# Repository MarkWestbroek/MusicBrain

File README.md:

# MusicBrain

An open platform for playable instruments, recallable patches and musical
control. Build and play modular patches in your browser, run shared DSP on a
Teensy, and connect supported external hardware through MIDI, CV, gates and
relay switching.

MusicBrain started as a way to give analog rigs memory. It now also includes
digital synthesizers, samplers and effects. External audio paths can remain
analog; internal DSP and USB audio are digital. Recall of external equipment
depends on which parameters and connections its hardware can actually control.

**[Open the editor](https://editor.musicbrain.nl/)** ([in English](https://editor.musicbrain.nl/?lang=en)) ·
[Website](https://musicbrain.nl/) ·
[Firmware downloads](https://github.com/MarkWestbroek/MusicBrain/releases) ·
[Development log](doc/RELEASE-LOG.md)

## Start here

| I want to... | Start with |
|---|---|
| Hear and edit a patch without hardware | [Try it in the browser](#try-it-in-the-browser) |
| Play patches on a Teensy | [Use a Teensy](#use-a-teensy) |
| Build or extend the hardware | [Build hardware](#build-hardware) |
| Explore instruments and workflows | [Feature guide](#feature-guide) |
| Work on the code | [Develop locally](#develop-locally) |
| Understand the direction | [Where it is going](#where-it-is-going) |

## Current status

**Development snapshot: 9 October 2026.** This is an active development
project, not just scaffolding and not a finished hardware product family.
The firmware source identifies itself as **0.5.99**. The deployed editor,
downloadable firmware and published hardware releases can lag behind source;
check the release notes and the version reported by a connected device.

| Product | Name used in this repository/editor | Current scope |
|---|---|---|
| **Cortex** | Modular MB / MMB / modular-brain | Working rack editor, patcher, browser instruments, presets and Teensy link. Digital audio runs on Teensy 4.1. The external modular hardware system is in development; validation varies by board and function. |
| **Reflex** | Effect-switcher / guitar-switcher | Offline pedal-chain and patch editor with MIDI/relay-state simulation; firmware implementations and hardware designs exist. Do not assume Cortex's connection workflow or a production-ready build. |
| **Relay** | Amp-switcher / amp/speaker-switcher | Architecture and safety requirements; the editor mode is a placeholder. Not a verified amp/cab switching system. |

The browser runs the same C++ DSP kernels as the firmware for supported
modules, compiled to WebAssembly. Audio I/O and some routing use Web Audio.
Shared kernels do **not** guarantee identical behavior of every complete
patch: hardware I/O, CPU/memory limits and feature support differ. The
**Modules** tab's **Sim** column indicates module support; polyphony depends
on the patch and target, not a universal voice-count guarantee.

## Try it in the browser

No MusicBrain hardware or account is needed for the core editor and simulator.
Use a current Chrome or Edge browser for the most straightforward MIDI/USB
workflow; device access depends on browser support and permissions.

1. Open [the editor](https://editor.musicbrain.nl/) (add
  [`?lang=en`](https://editor.musicbrain.nl/?lang=en) for English; an English
  browser gets it automatically). It opens in **play mode**: a patch from
  the standard set, its front panel and an on-screen keyboard that also
  works on a phone. A short tour explains the controls; **?** repeats it.
2. Choose another patch from the list and play. The first key press starts
  the audio. A MIDI keyboard is optional; grant access when using Web MIDI.
  Start with a low listening volume.
3. Turn the knobs on the front panel. **Save** keeps your changes in the
  patch; **Look inside ▸** opens the full editor (rack, patcher, simulator).
4. Export the project as JSON to keep a portable copy; browser storage is
  not a backup.

If a patch stays silent, check that audio has started, that it reaches an
output and that its modules are supported in the simulator. Sampler and
lyric instruments also need their banks. Availability of newer examples
depends on the deployed editor version.

For background and bank workflows, read
[The simulator as an instrument](doc/browser-instrumenten.md).
For pedalboards, select **Effect-switcher** and follow the
[effect-switcher guide](editor/README.md#effect-switcher-editor); its
simulation visualizes switching rather than emulating the sound of every pedal.

## Use a Teensy

Start with a **Teensy 4.1**, a USB data cable and a computer. Sampler and
memory-heavy patches need PSRAM; sample/lyric banks use a microSD card.
The current firmware's audio connection is **USB**, not a standalone analog
headphone or line output. An assembled Cortex backplane is not required to
try the internal digital instruments.

1. Follow [Firmware distribution](doc/firmware-distributie.md): download a
  released `.hex` from the editor's **Teensy > Firmware** panel or
  [GitHub Releases](https://github.com/MarkWestbroek/MusicBrain/releases),
  and install it with [PJRC Teensy Loader](https://www.pjrc.com/teensy/loader.html).
  Browser-only flashing is still a proposal.
2. Connect through the editor's Teensy link, verify the reported version
  and send a supported patch. Close the link before flashing again.
3. Set up USB-audio monitoring and, if needed, transfer banks to the SD card.
  Follow [Teensy on a PC: audio, flashing and storage](doc/teensy-aan-de-pc.md)
  for the Windows workflow and common silent-output problems.

Start with a simple patch before trying large sample banks or many voices.
See [simulator/firmware parity](doc/sim-firmware-parity-plan.md) for the
development history and [release notes](doc/RELEASE-LOG.md) for later changes.

## Feature guide

The generated [module catalogue](doc/module-catalogus.md) lists every internal module with ports, controls, simulator status, firmware status and the example patches that use it (regenerate with `npm run catalog` in `editor/`).

The linked guides include both current behavior and dated development notes;
some are in Dutch. Check their status and version before treating a proposal
or an old limitation as current. A module panel is not proof that a physical
module exists or that every target supports it.

| Area | What to explore | Guide |
|---|---|---|
| Modular editing | Racks, signal-typed cables, live controls, patches, presets and polyphonic voice groups | [Editor](editor/README.md), [polyphony model](doc/uml/11-simulation-wasm.md) |
| Synthesis | Subtractive/FM/wavetable, DX7, Mutable Instruments ports, STK physical models and SID | [Browser instruments](doc/browser-instrumenten.md), [STK](doc/plans/stk-sound-module.md), [SID](doc/plans/sid.md) |
| Sampling | Multisample analysis, SF2 import, key/velocity zones, bank transfer and SD streaming | [Browser instruments](doc/browser-instrumenten.md), [Teensy storage](doc/teensy-aan-de-pc.md#3-de-sd-kaart-voor-de-sampler) |
| Effects | Filters, delays, chorus, phasers, reverbs, pitch effects, compressors and EQ | [Release log](doc/RELEASE-LOG.md), [compressors](doc/plans/vintage-compressors.md), [EQ](doc/plans/vintage-eq.md) |
| Voice and audio input | External audio/vocoder, ZANG lyric banks and voice-synthesis experiments | [Zang](doc/plans/zingende-stemmen.md), [voice as an instrument](doc/plans/stem-als-instrument.md), [local speech generation](tools/piper-tts/README.md) |
| Play mode | Front panels, a touch keyboard and a Trautonium-style ribbon on the phone, a guided tour, English/Dutch, a four-track overdub recorder (free recording, then loop a region and punch in), one tempo per patch with tap tempo and MIDI clock | [Editor: play mode](editor/README.md#speelmodus-en-front), [overdub](doc/plans/overdub.md), [tempo](doc/plans/tempo.md) |
| Classic instruments | Trautonium (MIXTUR), Ondes Martenot with its Palme and Métallique speakers, Fairlight CMI (8-bit sampler mode and waveform synthesis drawn on a green-on-black PAGE 4), an arpeggiator, organ, e-piano, Mellotron, CS-80 brass and more | [Release log](doc/RELEASE-LOG.md), [Fairlight](doc/plans/fairlight.md), [module catalogue](doc/module-catalogus.md) |
| Performance control | MIDI, CC, aftertouch, control-surface feedback and touch/phone experiments | [Roto-Control](doc/plans/control-surface.md), [MPE status](doc/plans/mpe.md), [Snaarbank](doc/snaarbank-testlab.md) |
| Patch creation tools | Recipes, optional AI assistance and project-file editing through MCP | [Recipes](doc/plans/patch-recept.md), [MCP tools](tools/mmb-mcp/README.md) |
| A/B and morph | Compare and interpolate patches on the same rack; firmware support is incomplete | [Morph status and limits](doc/plans/morph-a-b.md) |

The core editor does not require an AI service. AI-assisted workflows can
require separate provider configuration; local speech generation has its
own setup. They are optional, not prerequisites for making music.

## Build hardware

Cortex uses a Teensy-based backplane with function cards for conversion,
gates, controls and routing. **dCV** is the digital control representation;
DAC/ADC cards connect it to physical analog CV. Do not mix board generations
or assume that every connector present on a PCB is already supported by firmware.

1. Read the [system-generation overview](doc/systeem-v3-plan.md) and
  [Cortex busboard guide](hardware/schematics/musicbrain-busboard/README.md).
2. Select compatible cards from [hardware/schematics](hardware/schematics/)
  using the [SPI bus specification](doc/spi-bus-spec.md). Check each board's
  revision, status, pinouts, BOM/fabrication files and remaining work.
3. Verify power, orientation and the intended firmware before first power-up.
  A clean ERC/DRC or fabrication package is not evidence of a physically
  assembled and tested board. Check the documented validation before ordering.

For Reflex, start with the [guitar-switcher specification](doc/guitar-switcher-spec.md)
and [gswitch-brain status](hardware/schematics/gswitch-brain/README.md).
For Relay, read the [amp/speaker-switcher requirements](firmware/app-amp-switcher/README.md):
never treat an unverified relay design as safe for power-amp/speaker switching.

## Where it is going

The goal is one open workflow spanning browser instruments, embedded DSP and
controllable analog hardware, with portable patches and reusable components.
It is not a promise to make every existing analog knob or cable recallable.

- **Current work:** stabilize playing, patch changes and simulator/Teensy
  behavior; expand useful instruments and complete hardware integration.
  Track concrete work in the [backlog](doc/BACKLOG.md).
- **Partially implemented directions:** expressive control including
  [MPE](doc/plans/mpe.md), [patch morphing](doc/plans/morph-a-b.md) and
  richer voice workflows. Each plan records its own supported and open parts.
- **Research, not a delivery commitment:** [Instrument Lab](doc/plans/musicbrain-instrument-lab.md)
  for analog/hybrid voice circuits, [State-Graph Synthesis](doc/plans/state-graph-synthesis.md)
  with early material-memory experiments, and [instrument spinoffs](spinoffs/README.md).

[Requirements](doc/Requirements.md), [Plan](doc/Plan.md) and
[Plan v2](doc/Plan-v2.md) preserve the original thinking and development
history. They are **not** the current release checklist or getting-started guide.

## Develop locally

### Editor

Install a current Node.js LTS release with npm. From the repository root:

```powershell
cd editor
npm install
npm run dev
```

Open the URL Vite prints, usually `http://localhost:5173`. The development
server is also configured for local-network access; use it on a trusted network.
Run `npm run typecheck`, `npm test` and `npm run build` in the editor directory
when changing its code. See the [editor guide](editor/README.md) and
[WASM build instructions](tools/mmb-wasm/README.md) for details.

### Host firmware tests

The hardware-independent core can be built without a Teensy. Requirements:
CMake 3.20 or later and a C++17 compiler (MSVC, Clang or GCC).
From the repository root:

```powershell
cmake -S firmware -B firmware/build
cmake --build firmware/build
ctest --test-dir firmware/build --output-on-failure
```

For multi-configuration generators such as Visual Studio, pass `-C Debug`
to `ctest` when testing a Debug build. This host simulator tests control and
routing; it is distinct from the browser audio simulator and the Teensy build.

### Find your way around

| Location | Purpose |
|---|---|
| [editor](editor/) | React/TypeScript application, instruments, patch tools and simulator |
| [firmware/core](firmware/core/) and [firmware/hal](firmware/hal/) | Shared C++ control logic and hardware abstraction |
| [firmware/app-modular-brain](firmware/app-modular-brain/) | Cortex/Teensy application and module contract |
| [firmware/lib](firmware/lib/) | Shared DSP and third-party libraries |
| [firmware/app-effect-switcher](firmware/app-effect-switcher/) | Reflex firmware targets |
| [hardware](hardware/) | Board designs, generators and sourcing |
| [tools](tools/) | WASM builds, measurement, bank conversion, speech and MCP tooling |
| [doc](doc/) | Guides, specifications, plans and development history |

For architecture, use the [ADRs](doc/adr/README.md) and
[UML overview](doc/uml/README.md). Editor module definitions and firmware
share a tested contract; changes to ports and controls must stay aligned.
Include usage/status documentation with substantive changes, not only a log entry.
The [style guide](doc/styleguide.md) covers the editor and the Imprint-built website.
Website maintainers: see the [Imprint content update brief](doc/imprint-website-actualisatie-2026-09.md).

## License

MusicBrain's own code is MIT-licensed; see [LICENSE](LICENSE). Third-party
libraries and assets retain their respective licenses and notices; the
root license does not replace them. Check those terms before redistributing
firmware, sample banks or other bundled material.

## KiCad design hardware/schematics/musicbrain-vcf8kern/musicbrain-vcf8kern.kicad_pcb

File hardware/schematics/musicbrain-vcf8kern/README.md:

# musicbrain-vcf8kern — 8× multimode VCF-kernkaart (rev 0.1)

Kernkaart van het **poly-analog-spoor** (`doc/poly-analog-spec.md`, VCF8 +
B3/B7/B10): 8 identieke SSI2140-stemmen met **pole-mixing multimode** (8 modes
via een 4051 per stem), cutoff/Q vanuit de Brain via de SPI-bus. Staande
kaart achter de VCF8-backbone (kernslot-contract v1.1). **110×92, 4-laags
(In1/In2 = GND-planes), dubbelzijdig bestukt** (besluit 2026-07-21: per stem
gaat de pole-mix-ster + buffer-steun + ontkoppeling naar de B-zijde via JLC
PCBA; de SSI2140's op de top soldeer je zelf), passieven 0603.

**Schema = hiërarchisch/gepagineerd + bedraad** (2026-07-21): root +
**`in-uit-DACs`**-pagina + **1 pagina per stem** (`stem1`..`stem8`, identiek
op ref/net-suffix na). Elke stempagina toont de SSI2140 met **echte draadjes**
naar zijn lokale subcircuits (gm-trap-knopen, integrator-caps, EXPO-, Q- en
pole-mix-netwerk → 4051); de **tap-bus** (AINB, OUT1..OUT4) loopt als globale
labels (die fan-outen naar meerdere stages + de pole-mix, net als de OLED-bus
in het TD-12-interposer-schema). Cross-pagina-netten (VCUT/VQ/FMCVB/MOUT/MODE)
= globale labels = de kale PCB-netnamen (PCB-netten hebben géén `/`-prefix).
Bron: `gen_vcf8kern.py` (+`schlib_hier.py`). *Dicht maar leesbaar; kan verder
uitgespreid worden.*

**Status: routing af, reproduceerbaar DRC 0/0** (2026-07-31) — ERC 0,
netcheck OK, plaatsing net-bewust (v3), alle signalen + voedingen geroute.
Een volledige run van `gen_vcf8kern.py`, gevolgd door KiCad DRC met opnieuw
gevulde zones, geeft **0 violations + 0 unconnected**. De definitieve
handroutes staan in de generator; het PCB is dus niet afhankelijk van
handwerk in pcbnew. Recept + valkuilen: WERKWIJZE.md §"Dichte borden".
Dit is een **rev-0.1-validatiekaart**: verwacht een respin na de bench-test
(SSI2140-niveaus, pole-mix-matching, tune-lus).

## Architectuur

```
                          ┌───────────── per stem (×8) ──────────────┐
kernslot ─SCLK/SDIN/CS/LDAC─► 2× AD5754 (daisy) ─VCUTk─►54.9k─► EXPO(7) SSI2140
  (v1.1)  ─SCLK2/SDIN2/CS2──► DAC128S085 ─VQk─►13k─► Q CTRL(12)   4-pole cascade
          ─FMCV─►buffer─►100k─► EXPO(7)                           IN1→gm1..gm4→OUT4
J2 AUDIO IN ─►/5-buffer─► AINB ─►15k─► IN1 ... cascade ... OUT1..OUT4
                                    │
              taps E0=AINB,E1..E4=OUT1..OUT4 ─► 8 passieve som-sterren
                                    └─► 4051 (MODE0..2) ─► ×5-buffer ─► J3 AUDIO UIT
OUT4 (×8) ─► 4051 (TSEL0..2) ─► LM311 ─► TOUT (open-drain, TEN via 2N7002)
```

### SSI2140-cascade (datasheet Fig 3, SSOP-20 — zelf solderen)

⚠️ **Pinout datasheet-geverifieerd** (2026-07-20): de buildspec had pins 1–6
verwisseld. Correct: 1=OUT2 2=CAP2 3=IN2 4=OUT1 5=CAP1 **6=IN1 (ingang)**
7=EXPO 8=TEMPCO 9=Q VCA OUT 10=GND 11=V− 12=Q CTRL 13=Q VCA IN+ 14=OUT4
15=CAP4 16=IN4 17=OUT3 18=CAP3 19=IN3 20=V+.

- Keten: `IN1(6)→gm1→OUT1(4)→IN2(3)→gm2→OUT2(1)→IN3(19)→gm3→OUT3(17)→IN4(16)
  →gm4→OUT4(14)`. Per trap **15k serie-in + 15k feedback + 200Ω shunt→GND +
  1nF C0G op CAPx** (Fig-20-schaling 15k voor buffer-load ≥5k). Elke cel
  inverteert → de pole-mix-tekens komen gratis.
- **Resonantie**: Q VCA OUT (pin 9, stroom) **direct op de IN1-knoop** →
  resonantie om de héle keten (SSM2040-karakter, Marks topologiekeuze). Zelf-
  oscillatie ≈ 222 µA; 13k vanaf de 0–3V3-Q-DAC geeft 254 µA = net voorbij.
- **Q-compensatie** (input-gain, Fig 14): AINB → 16.2k → Q VCA IN+ (13),
  1k pin13→GND — constante passband, géén extra opamp.
- **EXPO** (Fig 2b, tempco uit): cutoff-CV → 54.9k → pin 7, **1k pin7→GND,
  pin 8 open**. Temperatuurcompensatie via B10-tuningcycles i.p.v. de tempco-R.

### Pole-mixing (Fig 20 + AN701 Table 1)

5 taps (E0 = gebufferde ingang AINB, E1..E4 = OUT1..OUT4) → **8 passieve
gewogen-som-sterren** (één per mode) → een **4051** kiest de mode (MODE0..2) →
uitgangsbuffer. Gewicht *w* → weerstand **75k/w** (R_ref = 75k = Fig-20 RF);
gebruikte waarden 75k/37.4k/18.7k/12.4k. De passieve normalisatie (÷Σgewichten)
egaliseert de modeniveaus vanzelf. Tekens komen uit de trap-inversies, dus alle
weerstanden positief naar één knoop (AN701 §2).

**Modemenu (tap-zuinig, 15 mix-R/stem):**

| MODE0..2 | Mode | Gewichten (E0,E1,E2,E3,E4) |
|:--:|---|---|
| 000 | 4-pole LP | 0,0,0,0,1 |
| 001 | 3-pole LP | 0,0,0,1,0 |
| 010 | 2-pole LP | 0,0,1,0,0 |
| 011 | 1-pole LP | 0,1,0,0,0 |
| 100 | 2-pole HP | 1,2,1,0,0 |
| 101 | 2-pole BP | 0,1,1,0,0 |
| 110 | 4-pole BP | 0,0,1,2,1 |
| 111 | notch | 1,2,2,0,0 |

MODE gedeeld = **globale** modekeuze (v1); per-stem-modes = contract-extensie.

### CV — twee DAC-domeinen

- **Cutoff** (precisie, breed): **2× AD5754BREZ** in daisy op CS (16-bit,
  ±10 V-range, ADR421 2.5 V-ref — verplicht, non-R-variant). Offset binary
  (BIN→DVCC), EP=AVSS=−12V. VCUT1-4 = U31 A/B/C/D, VCUT5-8 = U32 A/B/C/D.
- **Q** (unipolair): **DAC128S085** octaal 12-bit (0–3V3), op de tweede
  SPI-keten (SCLK2/SDIN2/CS2). VQ1-8 = VOUTA-H → 13k → Q CTRL.
- **FMCV** (kernslot pin 5): audio-rate FM van de front-jack (via de
  backbone-attenuverter) → on-card buffer → per stem 100k op de EXPO-knoop.

### Tune (B10)

OUT4 van elke stem → **4051** (TSEL0..2 selecteren de stem) → **LM311**
comparator → **TOUT** (open-drain, pull-up op de backbone). **TEN** (geografisch)
schakelt via een **2N7002** de LM311-emitter naar GND: TEN hoog = déze kaart
drijft TOUT; anders hoog-Z. De Brain pollt via CS2, de RP2040-PIO meet de
periode/duty. Geen analoge tune-lijn over de bus.

## Kernslot-contract v1.1 (`doc/poly-analog-spec.md` B7)

Haakse male 2×12 aan de onderrand (J1), plugt in de verticale female 2×12 op
de backbone. Pins 1–6 spiegelen het busslot.

| Pin | Net | Pin | Net |
|--:|---|--:|---|
| 1 | GND | 2 | +12V |
| 3 | GND | 4 | −12V |
| 5 | **FMCV** | 6 | +3V3 |
| 7 | SCLK | 8 | GND |
| 9 | SDIN (AD5754 in) | 10 | SDO (daisy uit) |
| 11 | CS (SYNC) | 12 | LDAC |
| 13 | SCLK2 | 14 | SDIN2 (DAC128 in) |
| 15 | SDO2 (daisy uit) | 16 | CS2 |
| 17 | MODE0 | 18 | MODE1 |
| 19 | MODE2 | 20 | TSEL0 |
| 21 | TSEL1 | 22 | TSEL2 |
| 23 | TEN (geografisch) | 24 | TOUT (open-drain) |

**Audio** loopt níet door dit contract: **J2 = AUDIO IN, J3 = AUDIO UIT**
(1×10, jack8-contract: 1=GND, 2–9=stem1–8, 10=GND), **verticaal op de
bovenrand** (tegenover de kernslot). Verticale headers = van bovenaf geplugd
in de kaart-tot-kaart-gap; er is een plug-keepout omheen zodat het IDC-huis
vrij ligt (de lage 0603's ernaast lopen er in Z onderdoor).

## Kanaalmap (firmware)

| Stem | cutoff (AD5754) | Q (DAC128S085) | J2/J3 | tune-mux |
|--:|---|---|---|---|
| 1–4 | U31 A/B/C/D | VOUTA–D | pin 2–5 | Y4/Y7/Y6/Y5 |
| 5–8 | U32 A/B/C/D | VOUTE–H | pin 6–9 | Y2/Y0/Y1/Y3 |

De tune-mux-Y's zijn **geografisch** gemapt (2026-07-21, routing): linker
fysieke pinnen = helft-L (stem 1–4), rechter = helft-R (stem 5–8). Firmware-
tabel TSEL-code *n* (=Y*n*) → stem: **0→6, 1→7, 2→5, 3→8, 4→1, 5→4, 6→3, 7→2**.

- **POR/mute**: cutoff-DAC's centreren met marge (firmware); geen per-stem
  instelpots (B10-trimmerbeleid — het poly-probleem). Rev-0.1 legt géén
  DNP-trimvoetjes: de DAC-ranges + B10-tuning doen de kalibratie digitaal.

## Bestukken

- **JLC PCBA** voor alles uit de LCSC-catalogus: 4051/DAC128S085/TL074/LM311/
  2N7002/ADR421/passieven. ⚠️ **AD5754** (HTSSOP, ~€28 @LCSC) pas op een
  gevalideerd board (Route B) of los sourcen/consignment.
- **SSI2140** (SSOP-20, Sound Semiconductor — niet bij LCSC): **zelf
  nasolderen** (drag-solder, 0,635 pitch). De SSI-plekken op de top liggen
  vrij; **dubbelzijdige bestukking**: bottom-0603's vallen bij lokaal
  ironwerk niet af (FR4 geleidt slecht), maar het bord ligt niet vlak →
  foam/fixture onder de kaart bij het nasolderen.
- Rot van alle SMD in de JLC-preview checken vóór PCBA (nieuwe placement).

## Testen zonder backbone

Zie **`musicbrain-vcf8kern-testadapter`**: passief kaartje dat de kern direct
op de hoofd-SPI-bus zet (MOSI→SDIN+SDIN2, SCLK→SCLK+SCLK2, IRQ→CS2), met
MODE/TSEL-jumpers en een TOUT-pullup — bench-test vóór de VCF8-backbone bestaat.

## Openstaand vóór fab

- Fab-pakket genereren en de JLC-preview controleren; routing en DRC 0/0 zijn
  afgerond.
- RP2040-PIO-SPI-slave-test (poly-spec open punt) staat los van deze kaart.
- Pole-mix-matching: AN701 waarschuwt dat stopband-diepte volledig van de
  weerstandstolerantie afhangt — 1%-serie minimaal; bij respin evt. array's.
- Interne niveaus (SSI ±1 V, in-attenuatie ÷5 / uit-versterking ×5) op de
  bench meten en het noise-budget vastleggen.

## Aansluitoverzicht

De kaart heeft drie connectoren: **J1 KERNSLOT** (de kernslot-bus naar de
Brain: SPI, LDAC, TOUT, voedingen), **J2 AUDIO IN** en **J3 AUDIO UIT**
(elk 8 kanalen tussen twee GND-pinnen).

### Pinouts

Bovenaanzicht van het bord (kijkend op de pinnen); pin 1 = vierkant.
Gegenereerd uit het bordbestand met `hardware/kicad-generators/pinout_svg.py`.

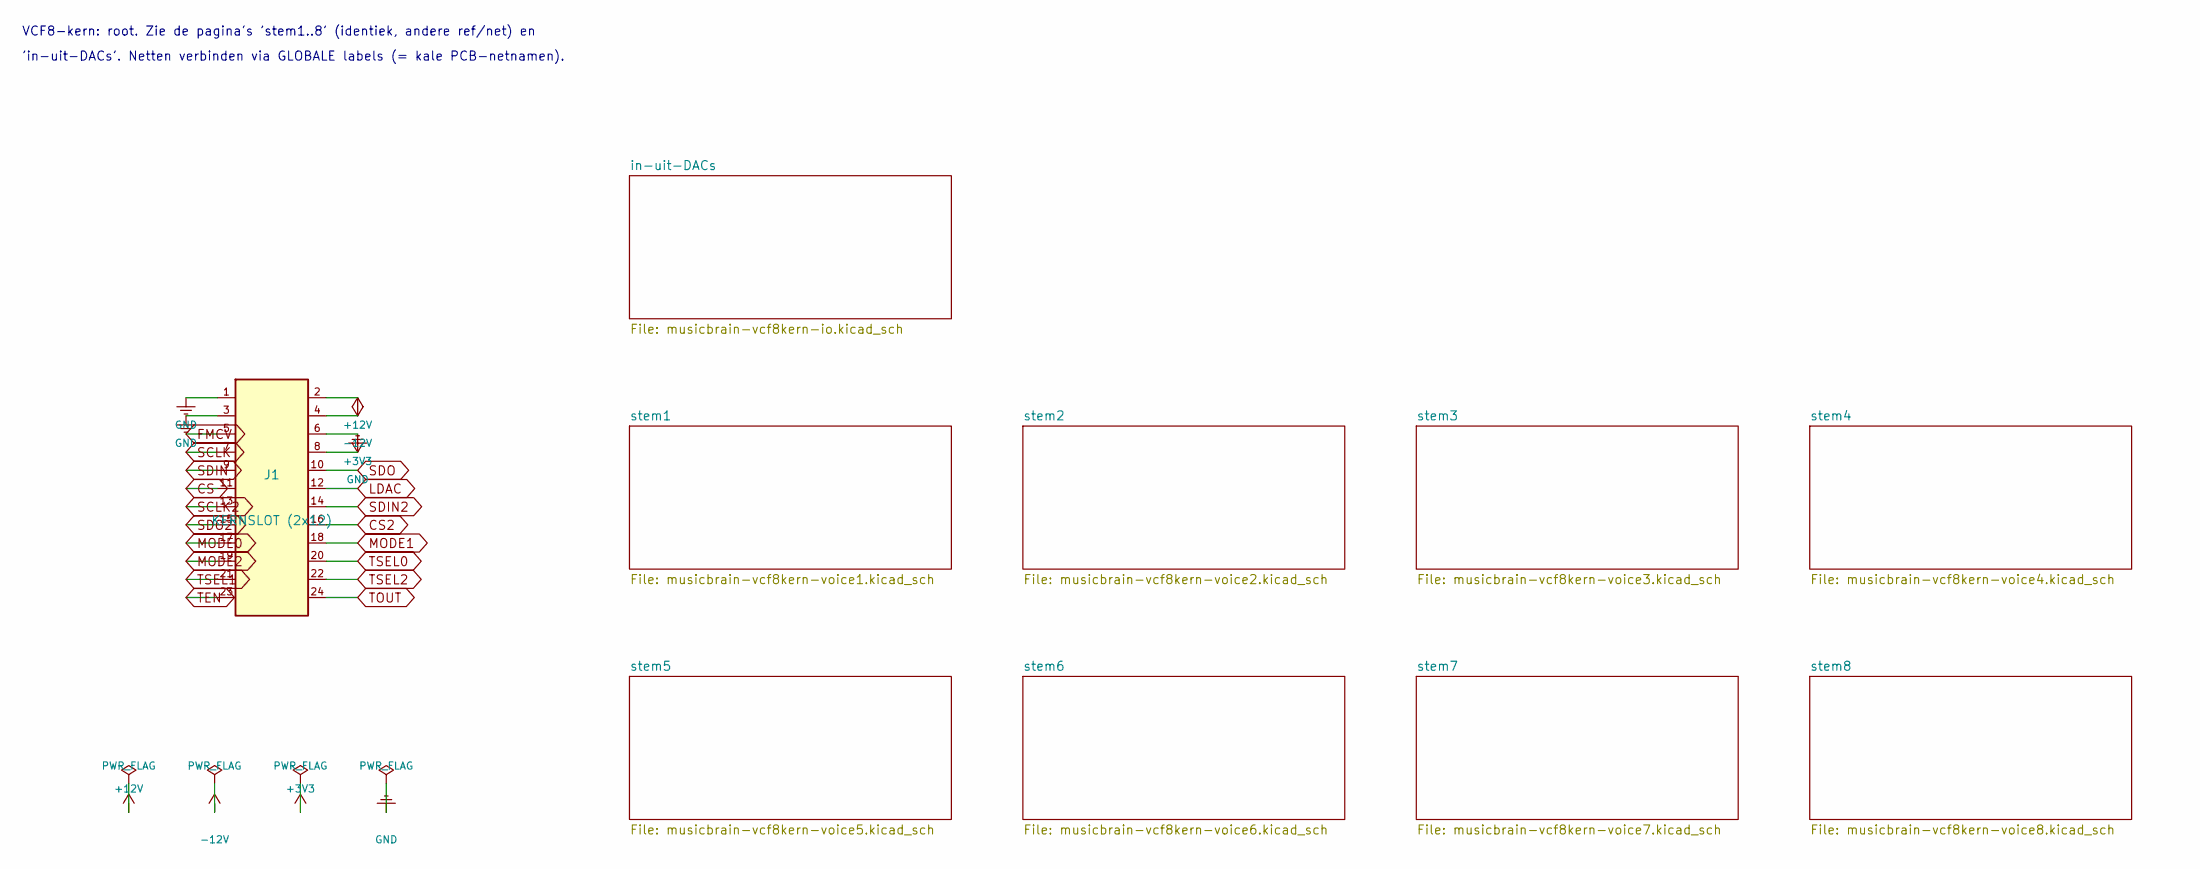
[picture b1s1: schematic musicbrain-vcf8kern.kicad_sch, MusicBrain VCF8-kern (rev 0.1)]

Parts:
J1: KERNSLOT (2x12)

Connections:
+3V3: J1.6; also elsewhere on the board
+12V: J1.2; also elsewhere on the board
-12V: J1.4; also elsewhere on the board
CS: J1.11; also elsewhere on the board
CS2: J1.16; also elsewhere on the board
FMCV: J1.5; also elsewhere on the board
GND: J1.1, J1.3, J1.8; also elsewhere on the board
LDAC: J1.12; also elsewhere on the board
MODE0: J1.17; also elsewhere on the board
MODE1: J1.18; also elsewhere on the board
MODE2: J1.19; also elsewhere on the board
SCLK: J1.7; also elsewhere on the board
SCLK2: J1.13; also elsewhere on the board
SDIN: J1.9; also elsewhere on the board
SDIN2: J1.14; also elsewhere on the board
SDO: J1.10; also elsewhere on the board
SDO2: J1.15; also elsewhere on the board
TEN: J1.23; also elsewhere on the board
TOUT: J1.24; also elsewhere on the board
TSEL0: J1.20; also elsewhere on the board
TSEL1: J1.21; also elsewhere on the board
TSEL2: J1.22; also elsewhere on the board

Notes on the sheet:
VCF8-kern: root. Zie de pagina's 'stem1..8' (identiek, andere ref/net) en
'in-uit-DACs'. Netten verbinden via GLOBALE labels (= kale PCB-netnamen).

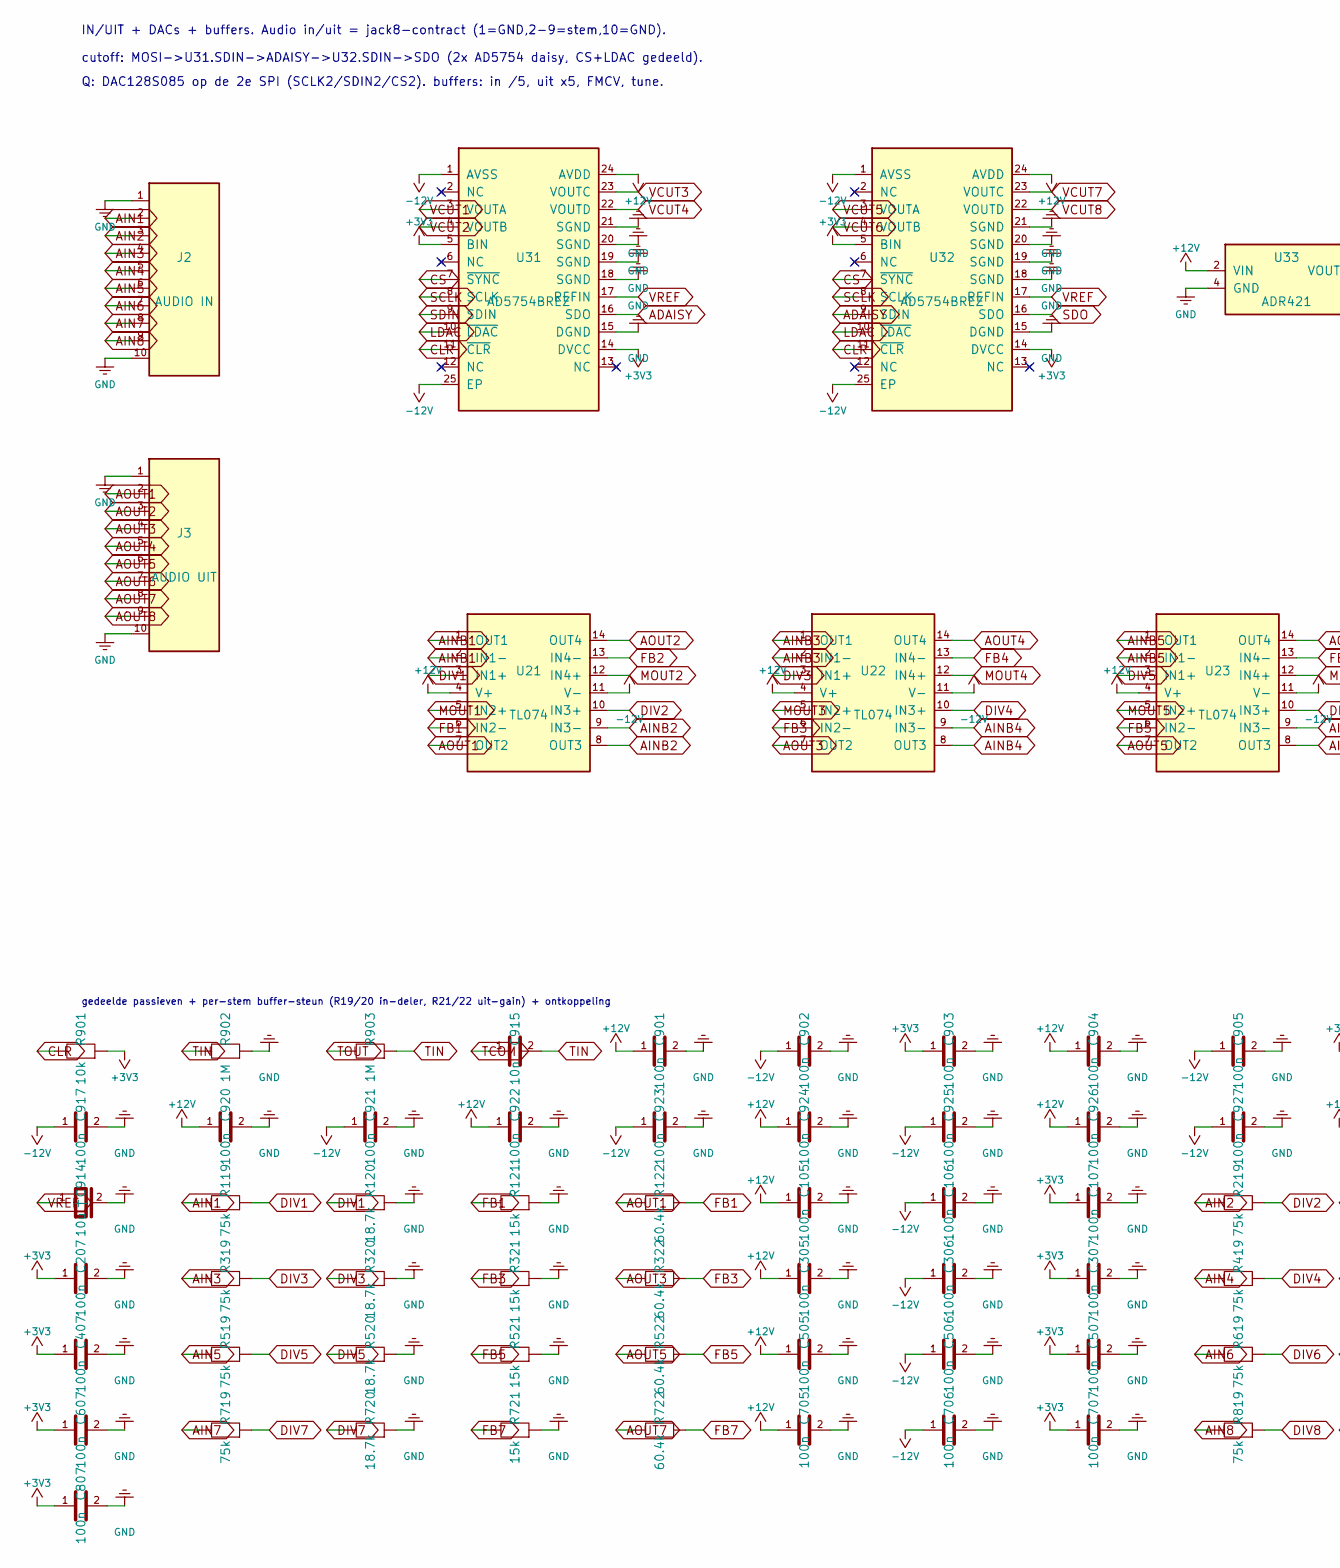
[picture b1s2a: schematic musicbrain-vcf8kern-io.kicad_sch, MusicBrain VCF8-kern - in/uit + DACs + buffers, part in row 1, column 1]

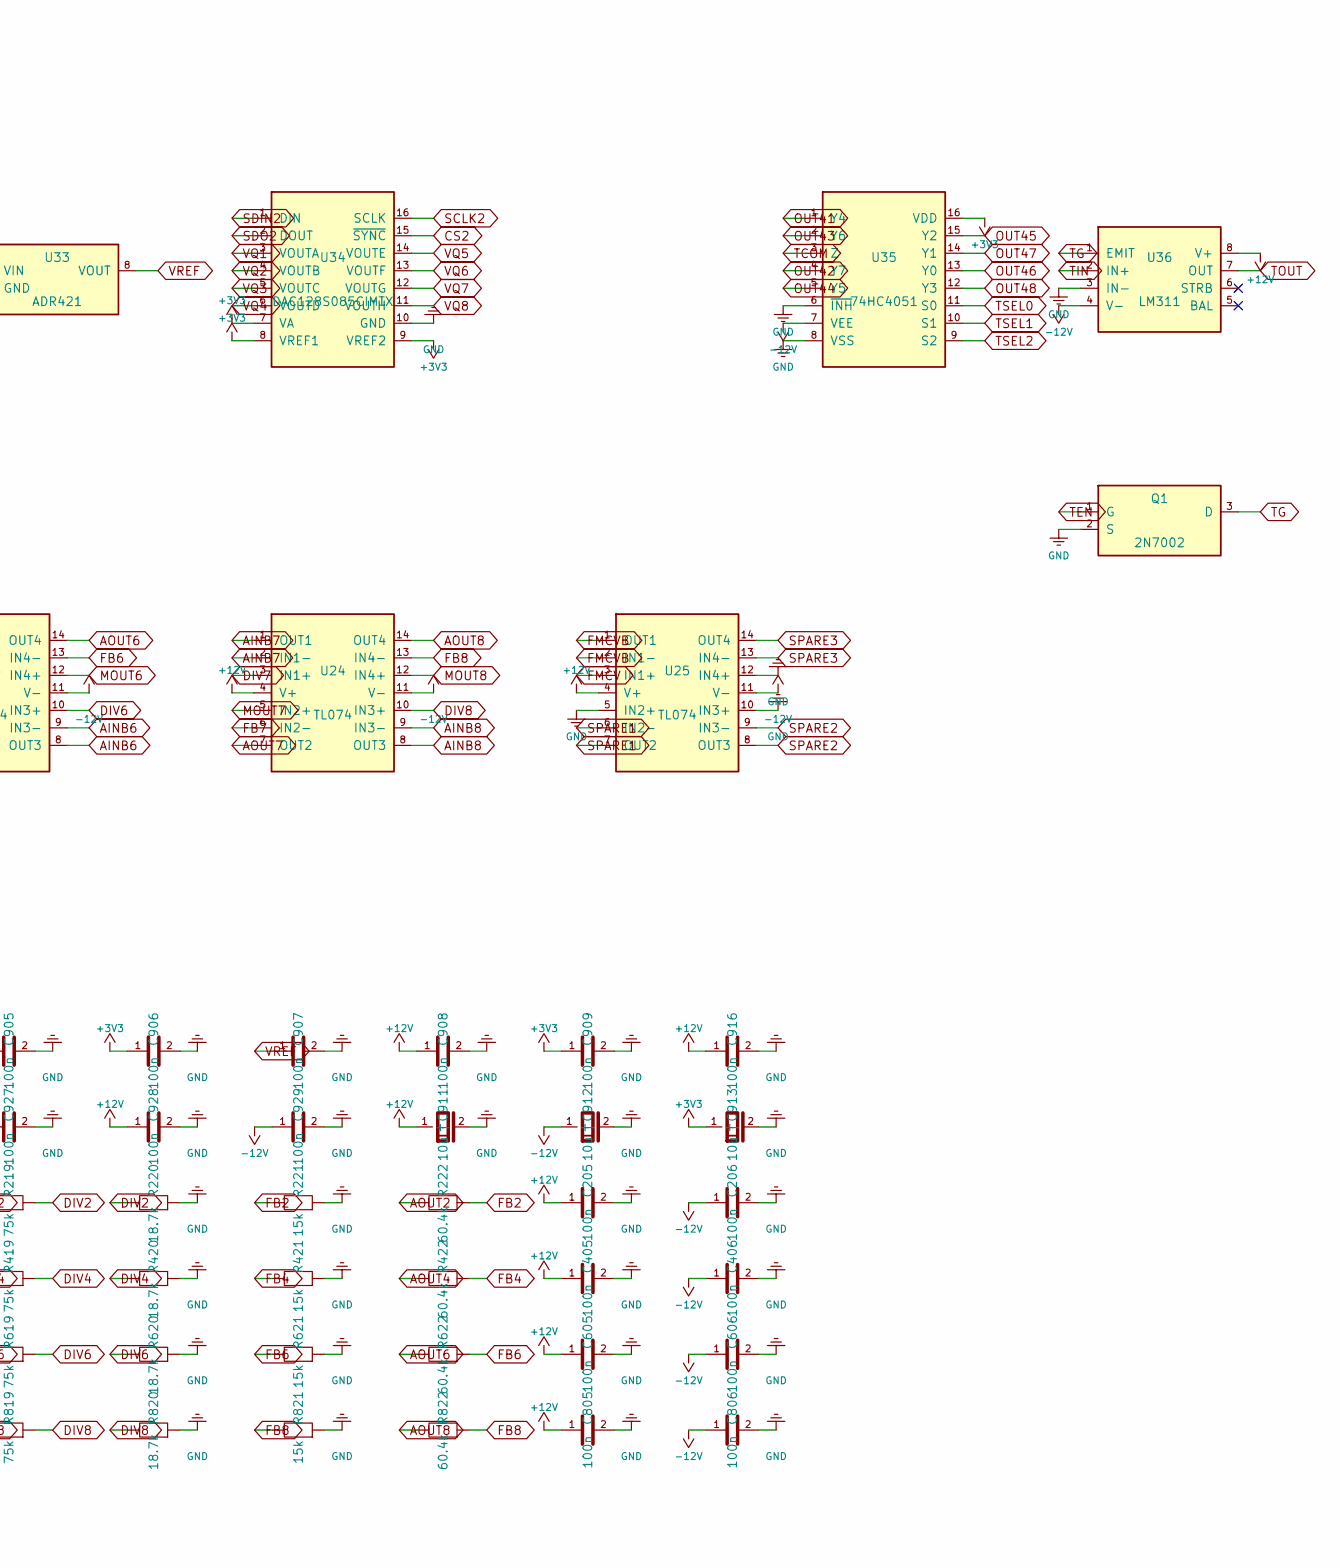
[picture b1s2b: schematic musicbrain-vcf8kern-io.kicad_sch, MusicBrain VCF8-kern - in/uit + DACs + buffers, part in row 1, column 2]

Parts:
C105, C106, C107, C205, C206, C207, C305, C306, C307, C405, C406, C407, C505, C506, C507, C605, C606, C607, C705, C706, C707, C805, C806, C807, C901, C902, C903, C904, C905, C906, C907, C908, C909, C916, C917, C920, C921, C922, C923, C924, C925, C926, C927, C928, C929: 100n; C_0603_1608Metric
C911, C912, C913, C914: 10u; CP_Elec_4x5.3
C915: 10n; C_0603_1608Metric
J2: AUDIO IN
J3: AUDIO UIT
Q1: 2N7002; SOT-23
R119, R219, R319, R419, R519, R619, R719, R819: 75k; R_0603_1608Metric
R120, R220, R320, R420, R520, R620, R720, R820: 18.7k; R_0603_1608Metric
R121, R221, R321, R421, R521, R621, R721, R821: 15k; R_0603_1608Metric
R122, R222, R322, R422, R522, R622, R722, R822: 60.4k; R_0603_1608Metric
R901: 10k; R_0603_1608Metric
R902, R903: 1M; R_0603_1608Metric
U21, U22, U23, U24, U25: TL074; TSSOP-14_4.4x5mm_P0.65mm
U31, U32: AD5754BREZ; HTSSOP-24-1EP_4.4x7.8mm_P0.65mm_EP3.2x5mm
U33: ADR421; SOIC-8_3.9x4.9mm_P1.27mm
U34: DAC128S085CIMTX; TSSOP-16_4.4x5mm_P0.65mm
U35: 74HC4051; TSSOP-16_4.4x5mm_P0.65mm
U36: LM311; SOIC-8_3.9x4.9mm_P1.27mm

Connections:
+3V3: C107.1, C207.1, C307.1, C407.1, C507.1, C607.1, C707.1, C807.1, C903.1, C906.1, C909.1, C913.1 (+), R901.2, U31.5 (BIN), U31.14 (DVCC), U32.5 (BIN), U32.14 (DVCC), U34.7 (VA), U34.8 (VREF1), U34.9 (VREF2), U35.16 (VDD); also elsewhere on the board
+12V: C105.1, C205.1, C305.1, C405.1, C505.1, C605.1, C705.1, C805.1, C901.1, C904.1, C908.1, C911.1 (+), C916.1, C920.1, C922.1, C924.1, C926.1, C928.1, U21.4 (V+), U22.4 (V+), U23.4 (V+), U24.4 (V+), U25.4 (V+), U31.24 (AVDD), U32.24 (AVDD), U33.2 (VIN), U36.8 (V+); also elsewhere on the board
-12V: C106.1, C206.1, C306.1, C406.1, C506.1, C606.1, C706.1, C806.1, C902.1, C905.1, C912.1 (+), C917.1, C921.1, C923.1, C925.1, C927.1, C929.1, U21.11 (V-), U22.11 (V-), U23.11 (V-), U24.11 (V-), U25.11 (V-), U31.1 (AVSS), U31.25 (EP), U32.1 (AVSS), U32.25 (EP), U35.7 (VEE), U36.4 (V-); also elsewhere on the board
ADAISY: U31.16 (SDO), U32.9 (SDIN)
AIN1: J2.2, R119.1
AIN2: J2.3, R219.1
AIN3: J2.4, R319.1
AIN4: J2.5, R419.1
AIN5: J2.6, R519.1
AIN6: J2.7, R619.1
AIN7: J2.8, R719.1
AIN8: J2.9, R819.1
AINB1: U21.1 (OUT1), U21.2 (IN1-); also elsewhere on the board
AINB2: U21.8 (OUT3), U21.9 (IN3-); also elsewhere on the board
AINB3: U22.1 (OUT1), U22.2 (IN1-); also elsewhere on the board
AINB4: U22.8 (OUT3), U22.9 (IN3-); also elsewhere on the board
AINB5: U23.1 (OUT1), U23.2 (IN1-); also elsewhere on the board
AINB6: U23.8 (OUT3), U23.9 (IN3-); also elsewhere on the board
AINB7: U24.1 (OUT1), U24.2 (IN1-); also elsewhere on the board
AINB8: U24.8 (OUT3), U24.9 (IN3-); also elsewhere on the board
AOUT1: J3.2, R122.1, U21.7 (OUT2)
AOUT2: J3.3, R222.1, U21.14 (OUT4)
AOUT3: J3.4, R322.1, U22.7 (OUT2)
AOUT4: J3.5, R422.1, U22.14 (OUT4)
AOUT5: J3.6, R522.1, U23.7 (OUT2)
AOUT6: J3.7, R622.1, U23.14 (OUT4)
AOUT7: J3.8, R722.1, U24.7 (OUT2)
AOUT8: J3.9, R822.1, U24.14 (OUT4)
CLR: R901.1, U31.11 (~CLR), U32.11 (~CLR)
CS: U31.7 (~SYNC), U32.7 (~SYNC); also elsewhere on the board
CS2: U34.15 (~SYNC); also elsewhere on the board
DIV1: R119.2, R120.1, U21.3 (IN1+)
DIV2: R219.2, R220.1, U21.10 (IN3+)
DIV3: R319.2, R320.1, U22.3 (IN1+)
DIV4: R419.2, R420.1, U22.10 (IN3+)
DIV5: R519.2, R520.1, U23.3 (IN1+)
DIV6: R619.2, R620.1, U23.10 (IN3+)
DIV7: R719.2, R720.1, U24.3 (IN1+)
DIV8: R819.2, R820.1, U24.10 (IN3+)
FB1: R121.1, R122.2, U21.6 (IN2-)
FB2: R221.1, R222.2, U21.13 (IN4-)
FB3: R321.1, R322.2, U22.6 (IN2-)
FB4: R421.1, R422.2, U22.13 (IN4-)
FB5: R521.1, R522.2, U23.6 (IN2-)
FB6: R621.1, R622.2, U23.13 (IN4-)
FB7: R721.1, R722.2, U24.6 (IN2-)
FB8: R821.1, R822.2, U24.13 (IN4-)
FMCV: U25.3 (IN1+); also elsewhere on the board
FMCVB: U25.1 (OUT1), U25.2 (IN1-); also elsewhere on the board
GND: C105.2, C106.2, C107.2, C205.2, C206.2, C207.2, C305.2, C306.2, C307.2, C405.2, C406.2, C407.2, C505.2, C506.2, C507.2, C605.2, C606.2, C607.2, C705.2, C706.2, C707.2, C805.2, C806.2, C807.2, C901.2, C902.2, C903.2, C904.2, C905.2, C906.2, C907.2, C908.2, C909.2, C911.2 (-), C912.2 (-), C913.2 (-), C914.2 (-), C916.2, C917.2, C920.2, C921.2, C922.2, C923.2, C924.2, C925.2, C926.2, C927.2, C928.2, C929.2, J2.1, J2.10, J3.1, J3.10, Q1.2 (S), R120.2, R121.2, R220.2, R221.2, R320.2, R321.2, R420.2, R421.2, R520.2, R521.2, R620.2, R621.2, R720.2, R721.2, R820.2, R821.2, R902.2, U25.5 (IN2+), U25.10 (IN3+), U25.12 (IN4+), U31.15 (DGND), U31.18 (SGND), U31.19 (SGND), U31.20 (SGND), U31.21 (SGND), U32.15 (DGND), U32.18 (SGND), U32.19 (SGND), U32.20 (SGND), U32.21 (SGND), U33.4 (GND), U34.10 (GND), U35.6 (~INH), U35.8 (VSS), U36.3 (IN-); also elsewhere on the board
LDAC: U31.10 (~LDAC), U32.10 (~LDAC); also elsewhere on the board
MOUT1: U21.5 (IN2+); also elsewhere on the board
MOUT2: U21.12 (IN4+); also elsewhere on the board
MOUT3: U22.5 (IN2+); also elsewhere on the board
MOUT4: U22.12 (IN4+); also elsewhere on the board
MOUT5: U23.5 (IN2+); also elsewhere on the board
MOUT6: U23.12 (IN4+); also elsewhere on the board
MOUT7: U24.5 (IN2+); also elsewhere on the board
MOUT8: U24.12 (IN4+); also elsewhere on the board
OUT41: U35.1 (Y4); also elsewhere on the board
OUT42: U35.4 (Y7); also elsewhere on the board
OUT43: U35.2 (Y6); also elsewhere on the board
OUT44: U35.5 (Y5); also elsewhere on the board
OUT45: U35.15 (Y2); also elsewhere on the board
OUT46: U35.13 (Y0); also elsewhere on the board
OUT47: U35.14 (Y1); also elsewhere on the board
OUT48: U35.12 (Y3); also elsewhere on the board
SCLK: U31.8 (SCLK), U32.8 (SCLK); also elsewhere on the board
SCLK2: U34.16 (SCLK); also elsewhere on the board
SDIN: U31.9 (SDIN); also elsewhere on the board
SDIN2: U34.1 (DIN); also elsewhere on the board
SDO: U32.16 (SDO); also elsewhere on the board
SDO2: U34.2 (DOUT); also elsewhere on the board
SPARE1: U25.6 (IN2-), U25.7 (OUT2)
SPARE2: U25.8 (OUT3), U25.9 (IN3-)
SPARE3: U25.13 (IN4-), U25.14 (OUT4)
TCOM: C915.1, U35.3 (Z)
TEN: Q1.1 (G); also elsewhere on the board
TG: Q1.3 (D), U36.1 (EMIT)
TIN: C915.2, R902.1, R903.2, U36.2 (IN+)
TOUT: R903.1, U36.7 (OUT); also elsewhere on the board
TSEL0: U35.11 (S0); also elsewhere on the board
TSEL1: U35.10 (S1); also elsewhere on the board
TSEL2: U35.9 (S2); also elsewhere on the board
VCUT1: U31.3 (VOUTA); also elsewhere on the board
VCUT2: U31.4 (VOUTB); also elsewhere on the board
VCUT3: U31.23 (VOUTC); also elsewhere on the board
VCUT4: U31.22 (VOUTD); also elsewhere on the board
VCUT5: U32.3 (VOUTA); also elsewhere on the board
VCUT6: U32.4 (VOUTB); also elsewhere on the board
VCUT7: U32.23 (VOUTC); also elsewhere on the board
VCUT8: U32.22 (VOUTD); also elsewhere on the board
VQ1: U34.3 (VOUTA); also elsewhere on the board
VQ2: U34.4 (VOUTB); also elsewhere on the board
VQ3: U34.5 (VOUTC); also elsewhere on the board
VQ4: U34.6 (VOUTD); also elsewhere on the board
VQ5: U34.14 (VOUTE); also elsewhere on the board
VQ6: U34.13 (VOUTF); also elsewhere on the board
VQ7: U34.12 (VOUTG); also elsewhere on the board
VQ8: U34.11 (VOUTH); also elsewhere on the board
VREF: C907.1, C914.1 (+), U31.17 (REFIN), U32.17 (REFIN), U33.8 (VOUT)

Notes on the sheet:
IN/UIT + DACs + buffers. Audio in/uit = jack8-contract (1=GND,2-9=stem,10=GND).
cutoff: MOSI->U31.SDIN->ADAISY->U32.SDIN->SDO (2x AD5754 daisy, CS+LDAC gedeeld).
Q: DAC128S085 op de 2e SPI (SCLK2/SDIN2/CS2). buffers: in /5, uit x5, FMCV, tune.
gedeelde passieven + per-stem buffer-steun (R19/20 in-deler, R21/22 uit-gain) + ontkoppeling

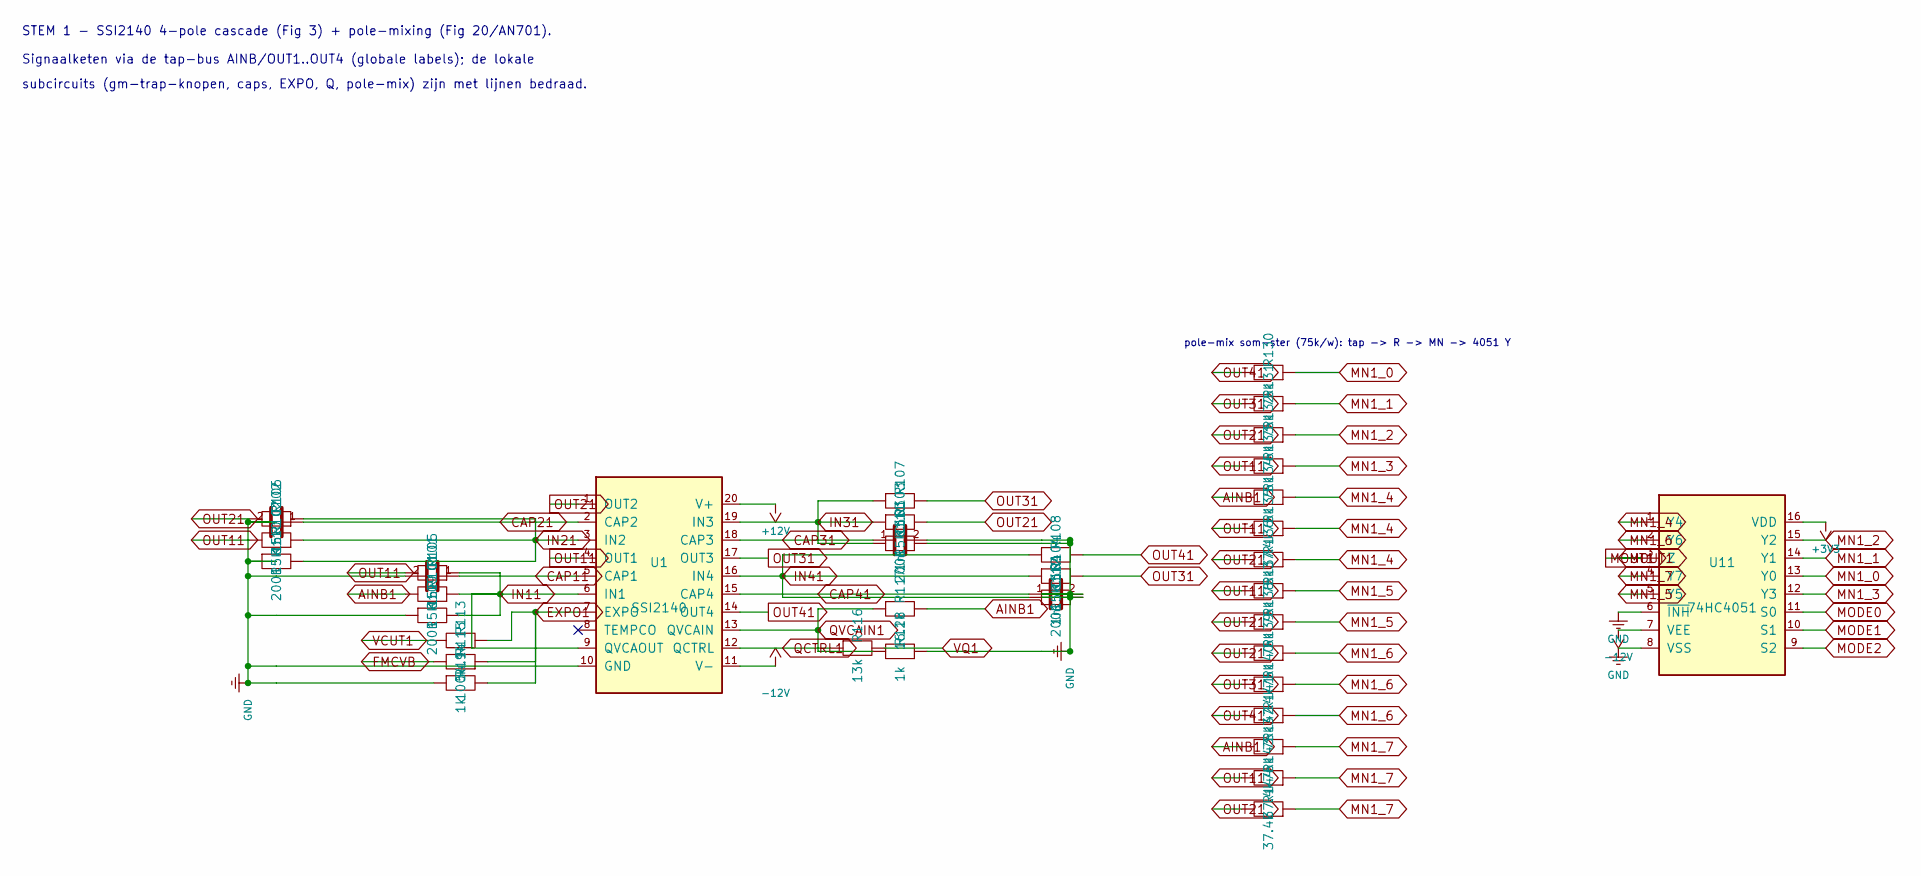
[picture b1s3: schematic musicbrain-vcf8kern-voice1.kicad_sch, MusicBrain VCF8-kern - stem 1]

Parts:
C101, C102, C103, C104: 1n; C_0603_1608Metric
R101, R102, R103, R104, R105, R106, R107, R108: 15k; R_0603_1608Metric
R109, R110, R111, R112: 200R; R_0603_1608Metric
R113: 54.9k; R_0603_1608Metric
R114, R118: 1k; R_0603_1608Metric
R115: 100k; R_0603_1608Metric
R116: 13k; R_0603_1608Metric
R117: 16.2k; R_0603_1608Metric
R130, R131, R132, R133, R134, R136, R137, R138, R139, R141, R142: 75k; R_0603_1608Metric
R135, R140, R143, R144: 37.4k; R_0603_1608Metric
U1: SSI2140; SSOP-20_3.9x8.7mm_P0.635mm
U11: 74HC4051; TSSOP-16_4.4x5mm_P0.65mm

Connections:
+3V3: U11.16 (VDD); also elsewhere on the board
+12V: U1.20 (V+); also elsewhere on the board
-12V: U1.11 (V-), U11.7 (VEE); also elsewhere on the board
AINB1: R101.1, R117.1, R134.1, R142.1; also elsewhere on the board
CAP11: C101.1, U1.5 (CAP1)
CAP21: C102.1, U1.2 (CAP2)
CAP31: C103.1, U1.18 (CAP3)
CAP41: C104.1, U1.15 (CAP4)
EXPO1: R113.2, R114.1, R115.2, U1.7 (EXPO)
FMCVB: R115.1; also elsewhere on the board
GND: C101.2, C102.2, C103.2, C104.2, R109.2, R110.2, R111.2, R112.2, R114.2, R118.2, U1.10 (GND), U11.6 (~INH), U11.8 (VSS); also elsewhere on the board
IN11: R101.2, R105.2, R109.1, U1.6 (IN1), U1.9 (QVCAOUT)
IN21: R102.2, R106.2, R110.1, U1.3 (IN2)
IN31: R103.2, R107.2, R111.1, U1.19 (IN3)
IN41: R104.2, R108.2, R112.1, U1.16 (IN4)
MN1_0: R130.2, U11.13 (Y0)
MN1_1: R131.2, U11.14 (Y1)
MN1_2: R132.2, U11.15 (Y2)
MN1_3: R133.2, U11.12 (Y3)
MN1_4: R134.2, R135.2, R136.2, U11.1 (Y4)
MN1_5: R137.2, R138.2, U11.5 (Y5)
MN1_6: R139.2, R140.2, R141.2, U11.2 (Y6)
MN1_7: R142.2, R143.2, R144.2, U11.4 (Y7)
MODE0: U11.11 (S0); also elsewhere on the board
MODE1: U11.10 (S1); also elsewhere on the board
MODE2: U11.9 (S2); also elsewhere on the board
MOUT1: U11.3 (Z); also elsewhere on the board
OUT11: R102.1, R105.1, R133.1, R135.1, R137.1, R143.1, U1.4 (OUT1)
OUT21: R103.1, R106.1, R132.1, R136.1, R138.1, R139.1, R144.1, U1.1 (OUT2)
OUT31: R104.1, R107.1, R131.1, R140.1, U1.17 (OUT3)
OUT41: R108.1, R130.1, R141.1, U1.14 (OUT4); also elsewhere on the board
QCTRL1: R116.2, U1.12 (QCTRL)
QVCAIN1: R117.2, R118.1, U1.13 (QVCAIN)
VCUT1: R113.1; also elsewhere on the board
VQ1: R116.1; also elsewhere on the board

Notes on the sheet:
pole-mix som-ster (75k/w): tap -> R -> MN -> 4051 Y
STEM 1 - SSI2140 4-pole cascade (Fig 3) + pole-mixing (Fig 20/AN701).
Signaalketen via de tap-bus AINB/OUT1..OUT4 (globale labels); de lokale
subcircuits (gm-trap-knopen, caps, EXPO, Q, pole-mix) zijn met lijnen bedraad.
